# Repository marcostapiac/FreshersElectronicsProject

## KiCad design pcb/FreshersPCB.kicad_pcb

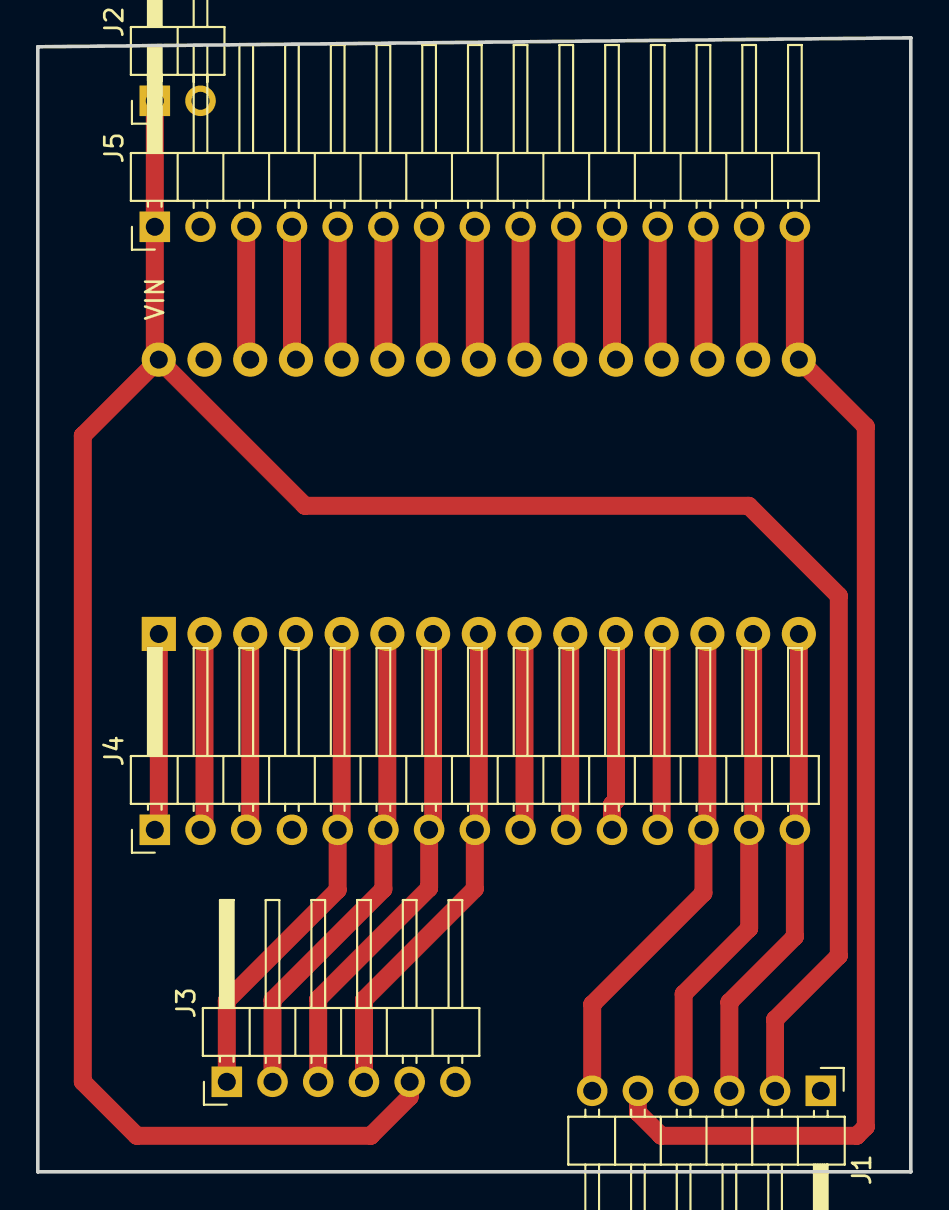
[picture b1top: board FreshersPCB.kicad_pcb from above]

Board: 2 copper layers, 48.5 x 63.0 mm, 6 parts (0 on the bottom side), 29 nets.

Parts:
J1, J3: CONN_01x06; Pin_Header_Angled_1x06_Pitch2.54mm
J2: CONN_01x02; Pin_Header_Angled_1x02_Pitch2.54mm
J4, J5: CONN_01x15; Pin_Header_Angled_1x15_Pitch2.54mm
U1: Arduino-Nano

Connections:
5v: J1.2, J2.1, J3.5, J5.1, U1.30
/GPS_EN: J3.3, J4.7, U1.7
/GPS_RX: J3.2, J4.6, U1.6
/GPS_TP: J3.4, J4.8, U1.8
/GPS_TX: J3.1, J4.5, U1.5
/MISO: J1.3, J4.15, U1.15
/MOSI: J1.4, J4.14, U1.14
/SCK: J1.5, J5.15, U1.16
/SS: J1.6, J4.13, U1.13
GND: J1.1, J2.2, J3.6, J4.4, J5.2, U1.4, U1.29
unnamed: J4.1, U1.1
unnamed: J4.2, U1.2
unnamed: J4.3, U1.3
unnamed: J4.9, U1.9
unnamed: J4.10, U1.10
unnamed: J4.11, U1.11
unnamed: J4.12, U1.12
unnamed: J5.3, U1.28
unnamed: J5.4, U1.27
unnamed: J5.5, U1.26
unnamed: J5.6, U1.25
unnamed: J5.7, U1.24
unnamed: J5.8, U1.23
unnamed: J5.9, U1.22
unnamed: J5.10, U1.21
unnamed: J5.11, U1.20
unnamed: J5.12, U1.19
unnamed: J5.13, U1.18
unnamed: J5.14, U1.17

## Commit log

2019-10-27 week1: started schematic
2019-10-27 update sumbodule use https
2019-11-03 finish schematic v1 and start pcb
2019-11-03 finish pcb v1
